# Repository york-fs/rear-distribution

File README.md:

# Rear Distribution Board

The rear distribution board is the central board of the LVS. It provides fusing for all other LVS components and
interfaces with the front, TSAC, and TS box distribution boards, as well as the inverter via AMPSEAL connections.

[Latest Release](https://github.com/york-fs/rear-distribution/releases/latest)
[Interactive BOM](https://york-fs.github.io/rear-distribution/ibom.html)

## Features

* **Blade Fuse Holders for All Other LVS components**
* **Fused 12 V and Shutdown Monitoring**
* **On-board microSD Slot**
* **UART Output for Radio Communication**

## Cloning

A recursive clone must be used to download the `kicad-library` repository:

    git clone --recursive https://github.com/york-fs/rear-distribution.git

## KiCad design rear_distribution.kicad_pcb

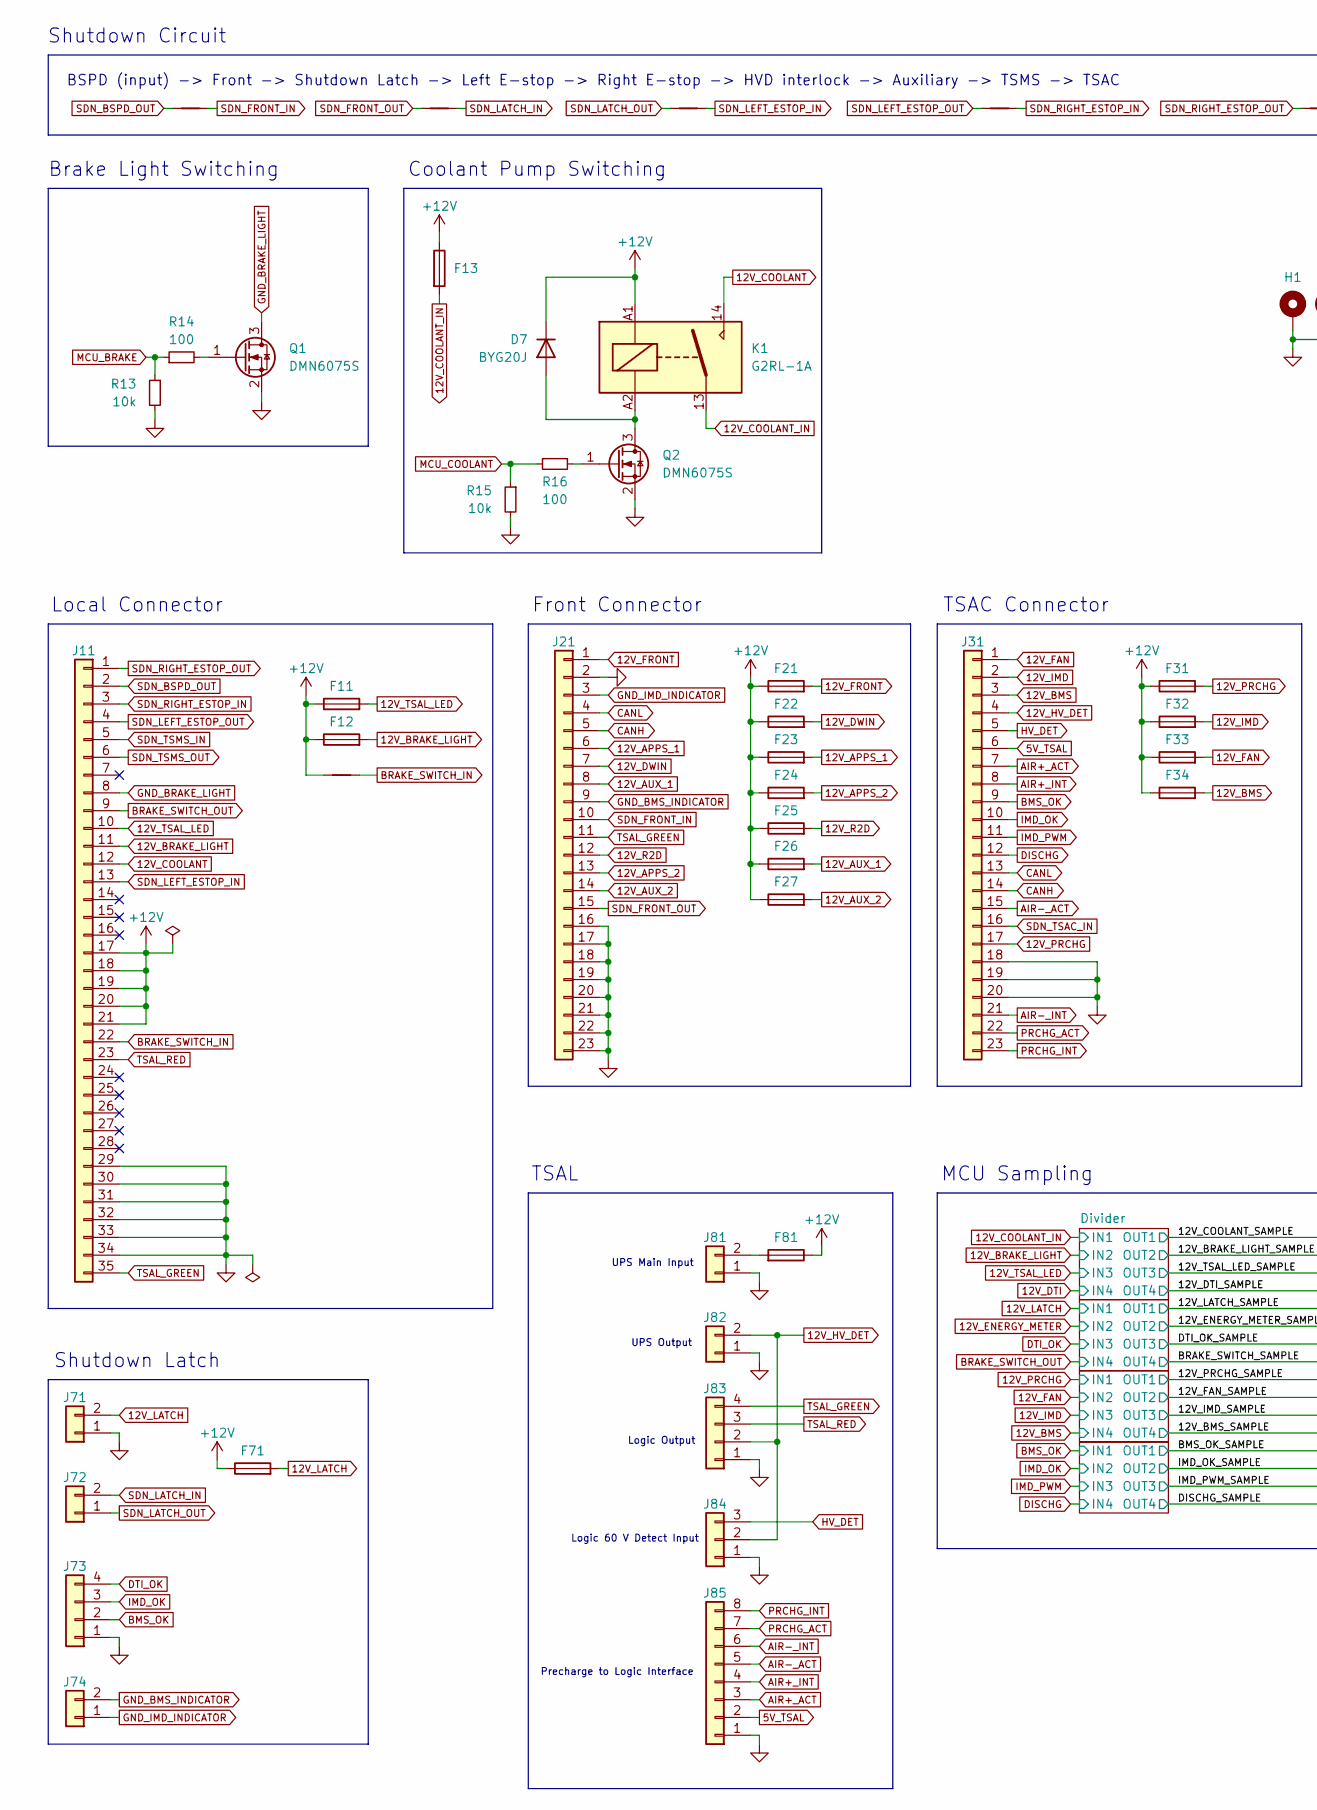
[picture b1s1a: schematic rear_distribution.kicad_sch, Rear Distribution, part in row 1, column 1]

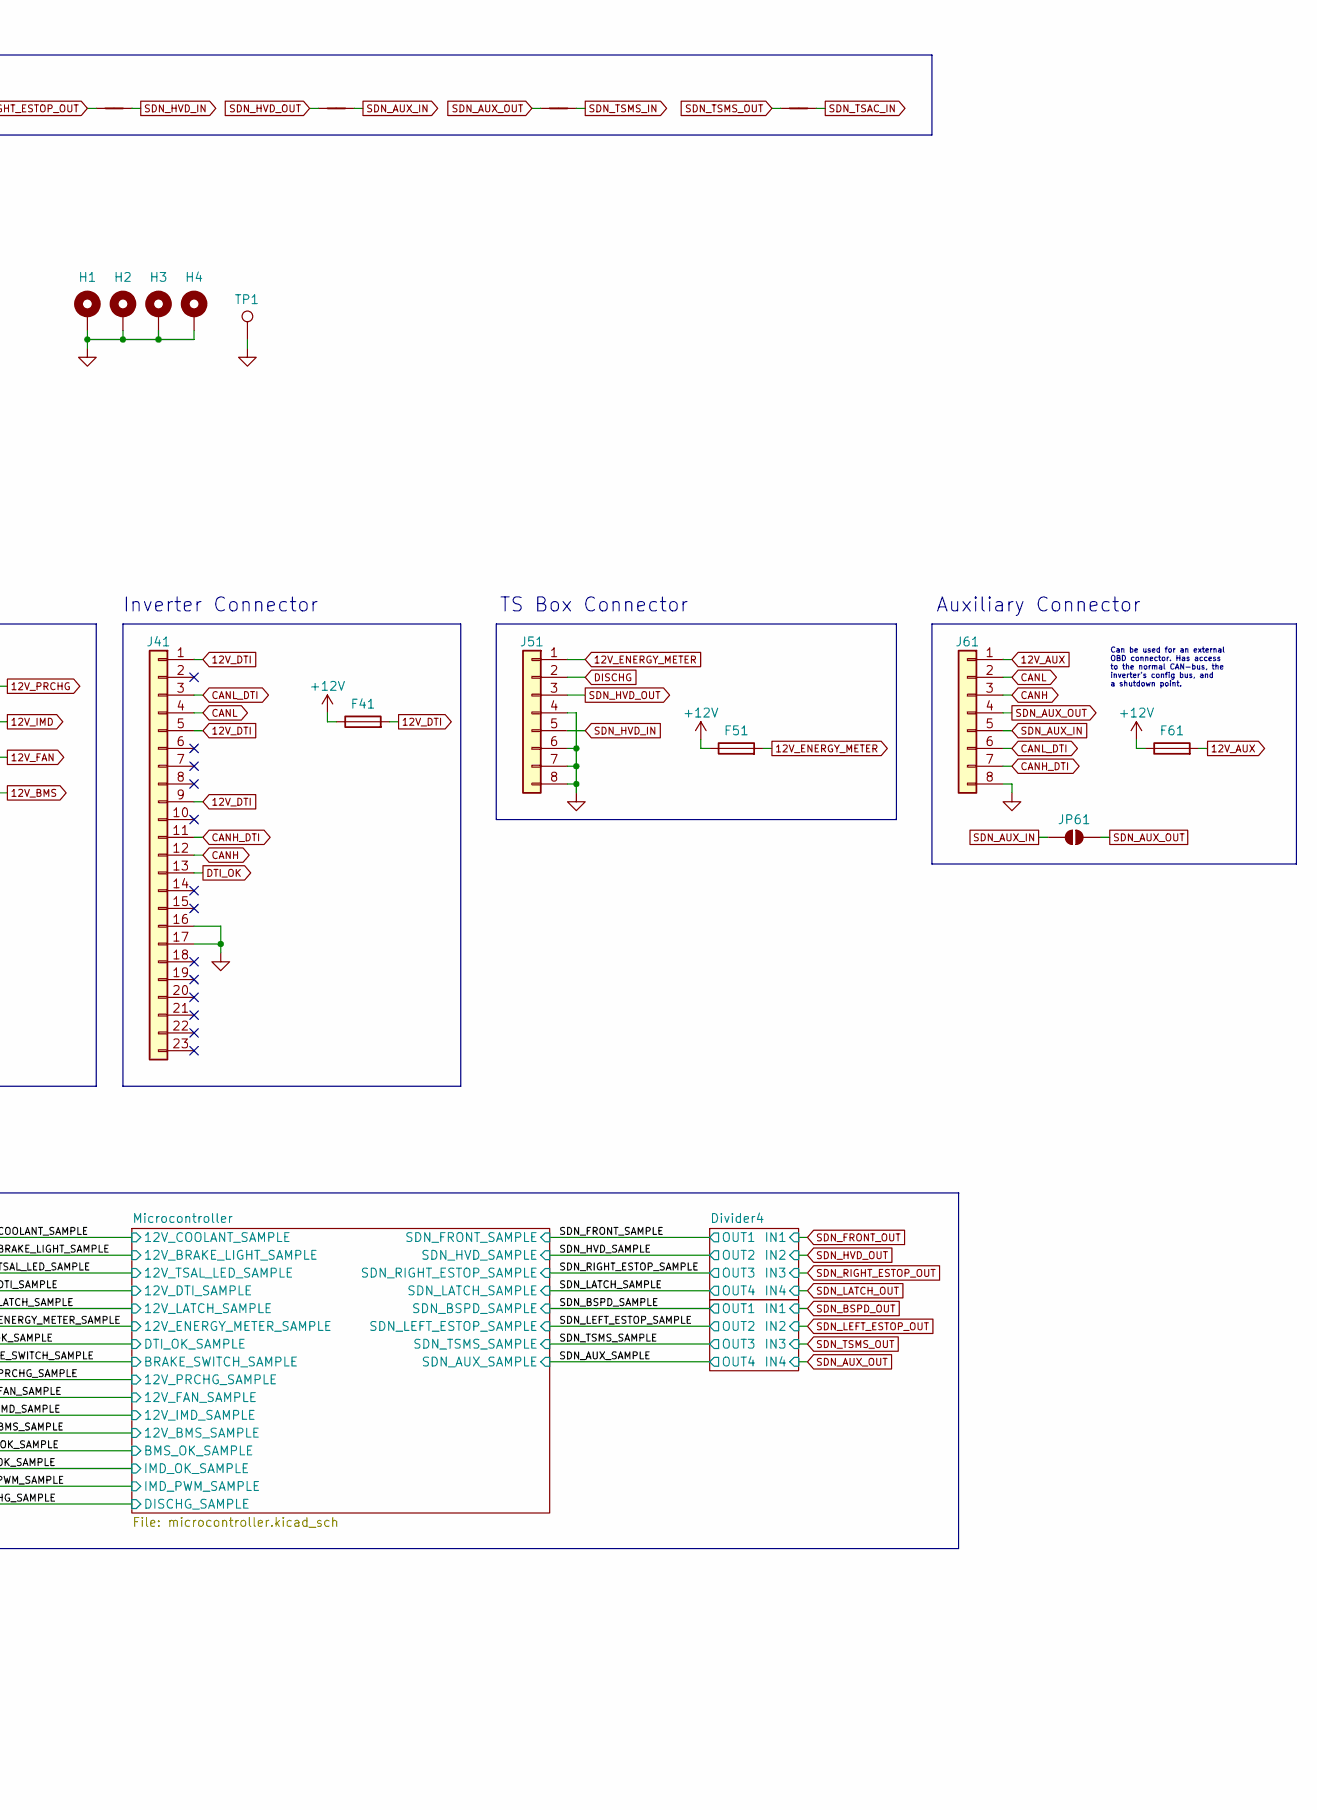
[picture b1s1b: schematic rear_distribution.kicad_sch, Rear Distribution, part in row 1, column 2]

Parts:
D7: BYG20J; D_SMA; Mfr # BYG20J-E3/TR; DigiKey # BYG20J-E3/TR3GICT-ND
F11, F12, F13, F21, F22, F23, F24, F25, F26, F27, F31, F32, F33, F34, F41, F51, F61, F71, F81: Fuse; Keystone_3557-2; Mfr # 3557-2; DigiKey # 36-3557-2-ND
H1, H2, H3, H4: MountingHole_Pad; MountingHole_3.2mm_M3_Pad_Via
J11: Conn_01x35; AMPSEAL-35-776163; Mfr # 776163-1; DigiKey # A106460-ND
J21, J31, J41: Conn_01x23; AMPSEAL-23-776087; Mfr # 776087-1; DigiKey # A107007-ND
J51, J61: Conn_01x08; AMPSEAL-8-776280; Mfr # 776280-1; DigiKey # 776280-1-ND
J71, J81: Conn_01x02; MolexMicrofitPlus1x2; Mfr # 2157601022; DigiKey # 900-2157601022-ND
J72: Conn_01x02; MolexMicrofitPlus1x2; Mfr # 2157601032; DigiKey # 900-2157601032-ND
J73, J83: Conn_01x04; MolexMicrofitPlus1x4; Mfr # 2157601004; DigiKey # 900-2157601004-ND
J74, J82: Conn_01x02; MolexMicrofitPlus1x2; Mfr # 2157601002; DigiKey # 900-2157601002-ND
J84: Conn_01x03; MolexMicrofitPlus1x3; Mfr # 2157601003; DigiKey # 900-2157601003-ND
J85: Conn_01x08; MolexMicrofitPlus1x8; Mfr # 2157601008; DigiKey # 900-2157601008-ND
JP61: SolderJumper_2_Open; SolderJumper-2_P1.3mm_Open_RoundedPad1.0x1.5mm
K1: G2RL-1A; Relay_SPST_Omron_G2RL-1A; Mfr # G2RL-1A-DC12; DigiKey # Z140-ND
NT2, NT3, NT4, NT5, NT6, NT7, NT8, NT9, NT10: NetTie_2; NetTie-2_SMD_Pad0.5mm
Q1, Q2: DMN6075S; SOT-23; Mfr # DMN6075S-7; DigiKey # DMN6075S-7DICT-ND
R13, R15: 10k; R_0603_1608Metric; Mfr # 0603WAF1002T5E; LCSC # C25804
R14, R16: 100; R_0603_1608Metric
TP1: TestPoint; TestPoint_Keystone_5019_Miniature; Mouser # 534-5019; DigiKey # 36-5019CT-ND

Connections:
5V_TSAL: J31.6, J85.2
12V_APPS_1: F23.2, J21.6
12V_APPS_2: F24.2, J21.13
12V_AUX: F61.2, J61.1
12V_AUX_1: F26.2, J21.8
12V_AUX_2: F27.2, J21.14
12V_BMS: F34.2, J31.3; also elsewhere on the board
12V_BRAKE_LIGHT: F12.2, J11.11; also elsewhere on the board
12V_COOLANT: J11.12, K1.14
12V_COOLANT_IN: F13.2, K1.13; also elsewhere on the board
12V_DTI: F41.2, J41.1, J41.5, J41.9; also elsewhere on the board
12V_DWIN: F22.2, J21.7
12V_ENERGY_METER: F51.2, J51.1; also elsewhere on the board
12V_FAN: F33.2, J31.1; also elsewhere on the board
12V_FRONT: F21.2, J21.1
12V_HV_DET: J31.4, J82.2, J83.2, J84.2
12V_IMD: F32.2, J31.2; also elsewhere on the board
12V_LATCH: F71.2, J71.2; also elsewhere on the board
12V_PRCHG: F31.2, J31.17; also elsewhere on the board
12V_R2D: F25.2, J21.12
12V_TSAL_LED: F11.2, J11.10; also elsewhere on the board
+12V: D7.1 (K), F11.1, F12.1, F13.1, F21.1, F22.1, F23.1, F24.1, F25.1, F26.1, F27.1, F31.1, F32.1, F33.1, F34.1, F41.1, F51.1, F61.1, F71.1, F81.1, J11.17, J11.18, J11.19, J11.20, J11.21, K1.A1, NT2.1; also elsewhere on the board
AIR+_ACT: J31.7, J85.3
AIR+_INT: J31.8, J85.4
AIR-_ACT: J31.15, J85.5
AIR-_INT: J31.21, J85.6
BMS_OK: J31.9, J73.2; also elsewhere on the board
BRAKE_SWITCH_IN: J11.22, NT2.2
BRAKE_SWITCH_OUT: J11.9; also elsewhere on the board
CANH: J21.5, J31.14, J41.12, J61.3; also elsewhere on the board
CANH_DTI: J41.11, J61.7
CANL: J21.4, J31.13, J41.4, J61.2; also elsewhere on the board
CANL_DTI: J41.3, J61.6
DISCHG: J31.12, J51.2; also elsewhere on the board
DTI_OK: J41.13, J73.4; also elsewhere on the board
GND: H1.1, H2.1, H3.1, H4.1, J11.29, J11.30, J11.31, J11.32, J11.33, J11.34, J21.2, J21.16, J21.17, J21.18, J21.19, J21.20, J21.21, J21.22, J21.23, J31.18, J31.19, J31.20, J41.16, J41.17, J51.4, J51.6, J51.7, J51.8, J61.8, J71.1, J73.1, J81.1, J82.1, J83.1, J84.1, J85.1, Q1.2 (S), Q2.2 (S), R13.2, R15.2, TP1.1; also elsewhere on the board
GND_BMS_INDICATOR: J21.9, J74.2
GND_BRAKE_LIGHT: J11.8, Q1.3 (D)
GND_IMD_INDICATOR: J21.3, J74.1
HV_DET: J31.5, J84.3
IMD_OK: J31.10, J73.3; also elsewhere on the board
IMD_PWM: J31.11; also elsewhere on the board
MCU_BRAKE: R13.1, R14.1; also elsewhere on the board
MCU_COOLANT: R15.1, R16.1; also elsewhere on the board
unnamed: D7.2 (A), K1.A2, Q2.3 (D)
unnamed: F81.2, J81.2
unnamed: Q1.1 (G), R14.2
unnamed: Q2.1 (G), R16.2
PRCHG_ACT: J31.22, J85.7
PRCHG_INT: J31.23, J85.8
SDN_AUX_IN: J61.5, JP61.1 (A), NT8.2
SDN_AUX_OUT: J61.4, JP61.2 (B), NT9.1; also elsewhere on the board
SDN_BSPD_OUT: J11.2, NT3.1; also elsewhere on the board
SDN_FRONT_IN: J21.10, NT3.2
SDN_FRONT_OUT: J21.15, NT4.1; also elsewhere on the board
SDN_HVD_IN: J51.5, NT7.2
SDN_HVD_OUT: J51.3, NT8.1; also elsewhere on the board
SDN_LATCH_IN: J72.2, NT4.2
SDN_LATCH_OUT: J72.1, NT5.1; also elsewhere on the board
SDN_LEFT_ESTOP_IN: J11.13, NT5.2
SDN_LEFT_ESTOP_OUT: J11.4, NT6.1; also elsewhere on the board
SDN_RIGHT_ESTOP_IN: J11.3, NT6.2
SDN_RIGHT_ESTOP_OUT: J11.1, NT7.1; also elsewhere on the board
SDN_TSAC_IN: J31.16, NT10.2
SDN_TSMS_IN: J11.5, NT9.2
SDN_TSMS_OUT: J11.6, NT10.1; also elsewhere on the board
TSAL_GREEN: J11.35, J21.11, J83.4
TSAL_RED: J11.23, J83.3

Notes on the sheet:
TSAL
Logic Output
UPS Main Input
Inverter Connector
UPS Output
Logic 60 V Detect Input
Auxiliary Connector
TSAC Connector
Local Connector
Precharge to Logic Interface
MCU Sampling
Can be used for an external OBD connector. Has access to the normal CAN-bus, the inverter's config bus, and a shutdown point.
Front Connector
BSPD (input) -> Front -> Shutdown Latch -> Left E-stop -> Right E-stop -> HVD interlock -> Auxiliary -> TSMS -> TSAC
Brake Light Switching
Shutdown Latch
Shutdown Circuit
Coolant Pump Switching
TS Box Connector

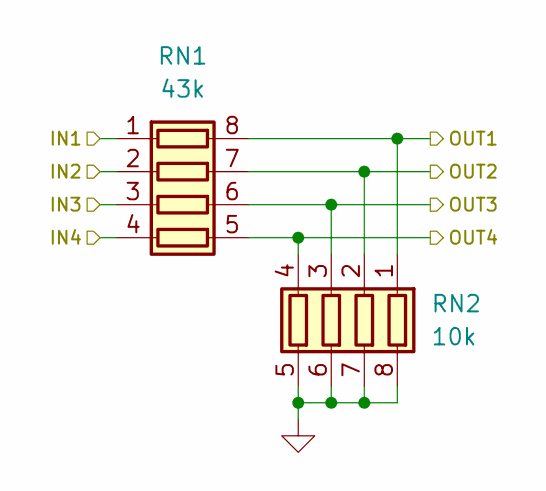
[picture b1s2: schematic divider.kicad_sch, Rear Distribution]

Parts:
RN1: 43k; R_Array_Convex_4x1206; Mfr # YC324-JK-0747KL; DigiKey # 13-YC324-JK-0747KLCT-ND
RN2: 10k; R_Array_Convex_4x1206; Mfr # YC324-FK-0710KL; DigiKey # 13-YC324-FK-0710KLCT-ND

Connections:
12V_BRAKE_LIGHT: RN1.2 (R2.1); also elsewhere on the board
12V_COOLANT_IN: RN1.1 (R1.1); also elsewhere on the board
12V_DTI: RN1.4 (R4.1); also elsewhere on the board
12V_TSAL_LED: RN1.3 (R3.1); also elsewhere on the board
/12V_BRAKE_LIGHT_SAMPLE: RN1.7 (R2.2), RN2.2 (R2.1); also elsewhere on the board
/12V_COOLANT_SAMPLE: RN1.8 (R1.2), RN2.1 (R1.1); also elsewhere on the board
/12V_DTI_SAMPLE: RN1.5 (R4.2), RN2.4 (R4.1); also elsewhere on the board
/12V_TSAL_LED_SAMPLE: RN1.6 (R3.2), RN2.3 (R3.1); also elsewhere on the board
GND: RN2.5 (R4.2), RN2.6 (R3.2), RN2.7 (R2.2), RN2.8 (R1.2); also elsewhere on the board

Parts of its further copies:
RN3, RN5, RN7, RN9, RN11: 43k; R_Array_Convex_4x1206; Mfr # YC324-JK-0747KL; DigiKey # 13-YC324-JK-0747KLCT-ND
RN4, RN6, RN8, RN10, RN12: 10k; R_Array_Convex_4x1206; Mfr # YC324-FK-0710KL; DigiKey # 13-YC324-FK-0710KLCT-ND

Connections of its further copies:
12V_BMS: RN5.4 (R4.1); also elsewhere on the board
12V_ENERGY_METER: RN3.2 (R2.1); also elsewhere on the board
12V_FAN: RN5.2 (R2.1); also elsewhere on the board
12V_IMD: RN5.3 (R3.1); also elsewhere on the board
12V_LATCH: RN3.1 (R1.1); also elsewhere on the board
12V_PRCHG: RN5.1 (R1.1); also elsewhere on the board
/12V_BMS_SAMPLE: RN5.5 (R4.2), RN6.4 (R4.1); also elsewhere on the board
/12V_ENERGY_METER_SAMPLE: RN3.7 (R2.2), RN4.2 (R2.1); also elsewhere on the board
/12V_FAN_SAMPLE: RN5.7 (R2.2), RN6.2 (R2.1); also elsewhere on the board
/12V_IMD_SAMPLE: RN5.6 (R3.2), RN6.3 (R3.1); also elsewhere on the board
/12V_LATCH_SAMPLE: RN3.8 (R1.2), RN4.1 (R1.1); also elsewhere on the board
/12V_PRCHG_SAMPLE: RN5.8 (R1.2), RN6.1 (R1.1); also elsewhere on the board
/BMS_OK_SAMPLE: RN7.8 (R1.2), RN8.1 (R1.1); also elsewhere on the board
/BRAKE_SWITCH_SAMPLE: RN3.5 (R4.2), RN4.4 (R4.1); also elsewhere on the board
/DISCHG_SAMPLE: RN7.5 (R4.2), RN8.4 (R4.1); also elsewhere on the board
/DTI_OK_SAMPLE: RN3.6 (R3.2), RN4.3 (R3.1); also elsewhere on the board
/IMD_OK_SAMPLE: RN7.7 (R2.2), RN8.2 (R2.1); also elsewhere on the board
/IMD_PWM_SAMPLE: RN7.6 (R3.2), RN8.3 (R3.1); also elsewhere on the board
/SDN_AUX_SAMPLE: RN11.5 (R4.2), RN12.4 (R4.1); also elsewhere on the board
/SDN_BSPD_SAMPLE: RN11.8 (R1.2), RN12.1 (R1.1); also elsewhere on the board
/SDN_FRONT_SAMPLE: RN9.8 (R1.2), RN10.1 (R1.1); also elsewhere on the board
/SDN_HVD_SAMPLE: RN9.7 (R2.2), RN10.2 (R2.1); also elsewhere on the board
/SDN_LATCH_SAMPLE: RN9.5 (R4.2), RN10.4 (R4.1); also elsewhere on the board
/SDN_LEFT_ESTOP_SAMPLE: RN11.7 (R2.2), RN12.2 (R2.1); also elsewhere on the board
/SDN_RIGHT_ESTOP_SAMPLE: RN9.6 (R3.2), RN10.3 (R3.1); also elsewhere on the board
/SDN_TSMS_SAMPLE: RN11.6 (R3.2), RN12.3 (R3.1); also elsewhere on the board
BMS_OK: RN7.1 (R1.1); also elsewhere on the board
BRAKE_SWITCH_OUT: RN3.4 (R4.1); also elsewhere on the board
DISCHG: RN7.4 (R4.1); also elsewhere on the board
DTI_OK: RN3.3 (R3.1); also elsewhere on the board
GND: RN4.5 (R4.2), RN4.6 (R3.2), RN4.7 (R2.2), RN4.8 (R1.2), RN6.5 (R4.2), RN6.6 (R3.2), RN6.7 (R2.2), RN6.8 (R1.2), RN8.5 (R4.2), RN8.6 (R3.2), RN8.7 (R2.2), RN8.8 (R1.2), RN10.5 (R4.2), RN10.6 (R3.2), RN10.7 (R2.2), RN10.8 (R1.2), RN12.5 (R4.2), RN12.6 (R3.2), RN12.7 (R2.2), RN12.8 (R1.2); also elsewhere on the board
IMD_OK: RN7.2 (R2.1); also elsewhere on the board
IMD_PWM: RN7.3 (R3.1); also elsewhere on the board
SDN_AUX_OUT: RN11.4 (R4.1); also elsewhere on the board
SDN_BSPD_OUT: RN11.1 (R1.1); also elsewhere on the board
SDN_FRONT_OUT: RN9.1 (R1.1); also elsewhere on the board
SDN_HVD_OUT: RN9.2 (R2.1); also elsewhere on the board
SDN_LATCH_OUT: RN9.4 (R4.1); also elsewhere on the board
SDN_LEFT_ESTOP_OUT: RN11.2 (R2.1); also elsewhere on the board
SDN_RIGHT_ESTOP_OUT: RN9.3 (R3.1); also elsewhere on the board
SDN_TSMS_OUT: RN11.3 (R3.1); also elsewhere on the board

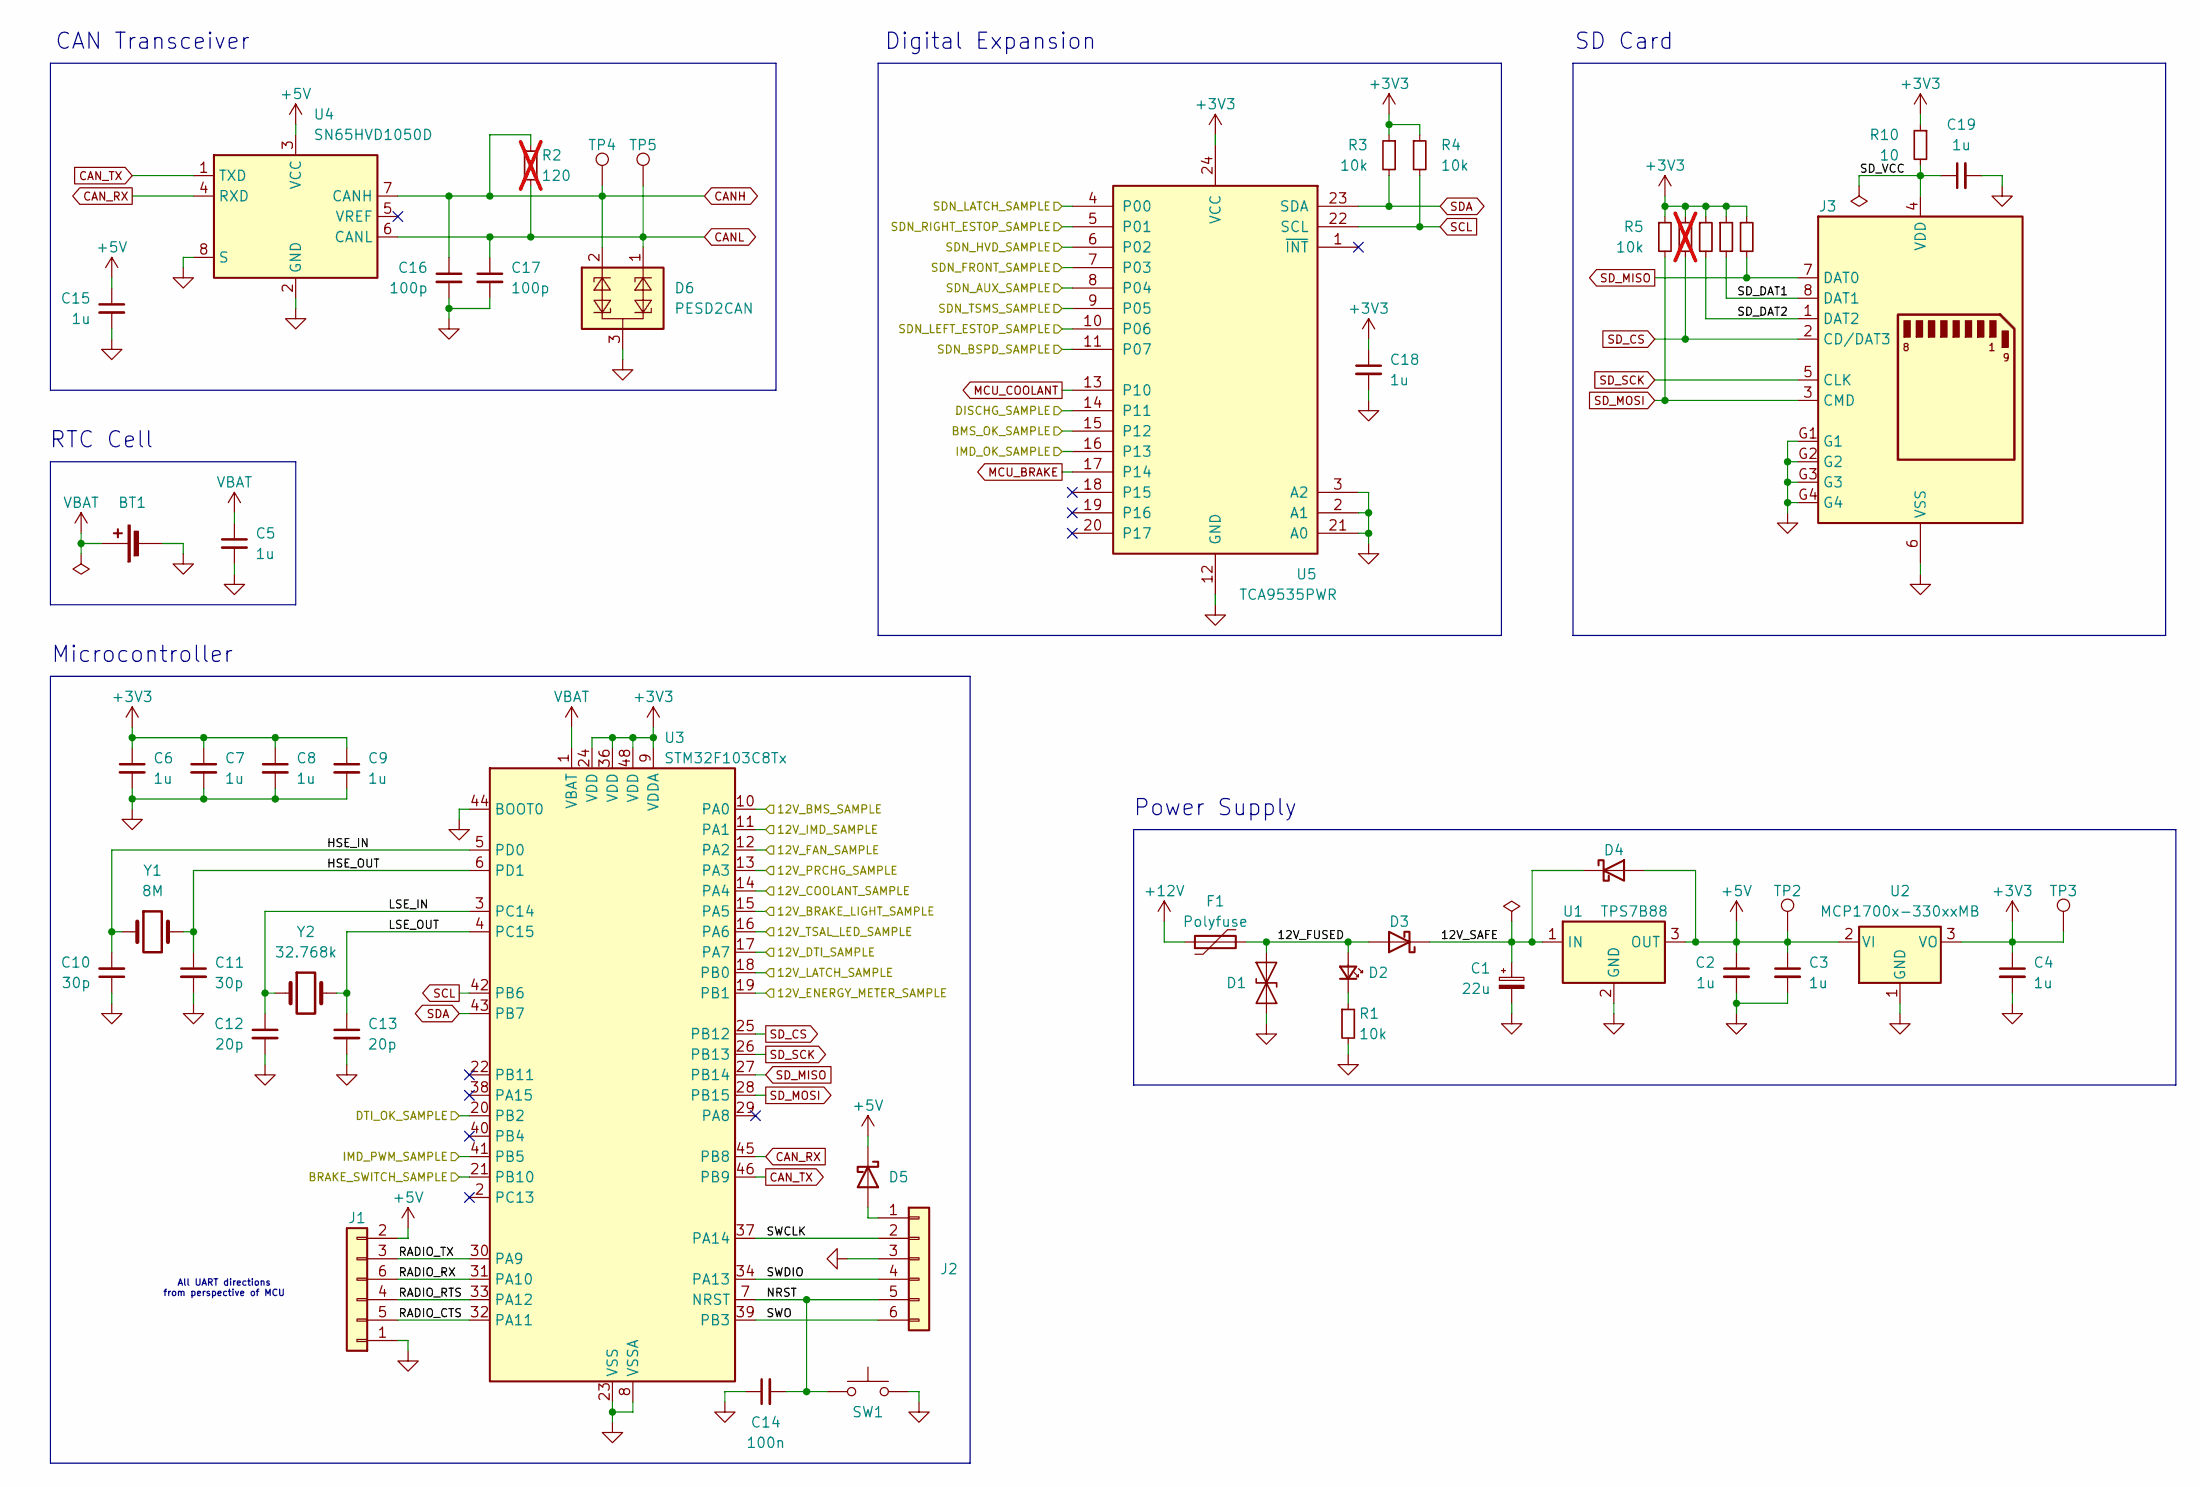
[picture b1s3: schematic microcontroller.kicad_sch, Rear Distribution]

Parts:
BT1: Battery_Cell; BAT-SMD_BS-CR2032-8
C1: 22u; CP_Elec_6.3x7.7; Mfr # EEEFK1J220XP; DigiKey # PCE3821CT-ND
C2, C3, C4, C5, C6, C7, C8, C9, C15, C18, C19: 1u; C_0603_1608Metric; Mfr # CL10B105KB8NQNC; LCSC # C5199872
C10, C11: 30p; C_0603_1608Metric; Mfr # GQM1875C2E300GB12D; DigiKey # 490-GQM1875C2E300GB12DCT-ND
C12, C13: 20p; C_0603_1608Metric
C14: 100n; C_0603_1608Metric; Mfr # CL10B104KB8NNNC; DigiKey # 1276-1000-1-ND
C16, C17: 100p; C_0603_1608Metric; Mfr # GCM1885C2A101JA16D; DigiKey # 490-4771-1-ND
D1: SMAJ24CA; D_SMA; Mfr # SMAJ24CA; DigiKey # SMAJ24CALFCT-ND
D2: LED_Small; LED_0603_1608Metric; Mfr # NCD0603R1; LCSC # C84263
D3, D4, D5: D_Schottky; D_SOD-323; Mfr # NSR0530H; DigiKey # NSR0530HT1GOSCT-ND
D6: PESD2CAN; SOT-23; Mfr # PESD2CAN,215; DigiKey # 1727-3891-1-ND
F1: Polyfuse; C_0805_2012Metric; Mfr # 0805L010/24YR; DigiKey # F11311CT-ND
J1: Conn_01x06; MolexMicrofitPlus2x3; Mfr # 2125280600; DigiKey # 900-2125280600-ND
J2: Conn_01x06; IDC-Connector-2x3; Mfr # HX JN1.27-2x3P ZZ H4.9; LCSC # C42372545
J3: 47219-2001; Molex_SD_Slot_47219-2001; Mfr # 472192001; DigiKey # WM6698CT-ND
R1, R3, R4, R5, R7, R8, R9: 10k; R_0603_1608Metric; Mfr # 0603WAF1002T5E; LCSC # C25804
R2: 120; R_0603_1608Metric; not fitted
R6: 10k; R_0603_1608Metric; Mfr # 0603WAF1002T5E; LCSC # C25804; not fitted
R10: 10; R_0603_1608Metric
SW1: SW_Push; SW_Push_1P1T_NO_Vertical_Wuerth_434133025816; Mfr # SKRPACE010; DigiKey # 4809-SKRPACE010CT-ND
TP2, TP3: TestPoint; TestPoint_Keystone_5000-5004_Miniature; Mouser # 534-5000; DigiKey # 36-5000-ND
TP4, TP5: TestPoint; TestPoint_THTPad_D2.0mm_Drill1.0mm
U1: TPS7B88; TO-252-2; Mfr # TPS7B8850QKVURQ1; DigiKey # 296-TPS7B8850QKVURQ1CT-ND
U2: MCP1700x-330xxMB; SOT-89-3; Mfr # MCP1700T-3302E/MB; DigiKey # MCP1700T3302EMBCT-ND
U3: STM32F103C8Tx; LQFP-48_7x7mm_P0.5mm; Mfr # STM32F103C8T6; DigiKey # 497-17666-1-ND
U4: SN65HVD1050D; SOIC-8_3.9x4.9mm_P1.27mm; Mfr # SN65HVD1050DR; DigiKey # 296-26335-1-ND
U5: TCA9535PWR; TSSOP-24_4.4x7.8mm_P0.65mm; Mfr # TCA9535PWR; DigiKey # 296-25129-1-ND
Y1: 8M; Crystal_SMD_5032-2Pin_5.0x3.2mm; Mfr # X50328MSB2GI; LCSC # C115962
Y2: 32.768k; Crystal_SMD_G8-2Pin_3.2x1.5mm

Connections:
+3V3: C4.1, C6.1, C7.1, C8.1, C9.1, C18.1, R3.1, R4.1, R5.1, R6.1, R7.1, R8.1, R9.1, R10.1, TP3.1, U2.3 (VO), U3.9 (VDDA), U3.24 (VDD), U3.36 (VDD), U3.48 (VDD), U5.24 (VCC)
+5V: C2.1, C3.1, C15.1, D4.2 (A), D5.1 (K), J1.2, TP2.1, U1.3 (OUT), U2.2 (VI), U4.3 (VCC)
+12V: F1.1; also elsewhere on the board
/12V_BMS_SAMPLE: U3.10 (PA0); also elsewhere on the board
/12V_BRAKE_LIGHT_SAMPLE: U3.15 (PA5); also elsewhere on the board
/12V_COOLANT_SAMPLE: U3.14 (PA4); also elsewhere on the board
/12V_DTI_SAMPLE: U3.17 (PA7); also elsewhere on the board
/12V_ENERGY_METER_SAMPLE: U3.19 (PB1); also elsewhere on the board
/12V_FAN_SAMPLE: U3.12 (PA2); also elsewhere on the board
/12V_IMD_SAMPLE: U3.11 (PA1); also elsewhere on the board
/12V_LATCH_SAMPLE: U3.18 (PB0); also elsewhere on the board
/12V_PRCHG_SAMPLE: U3.13 (PA3); also elsewhere on the board
/12V_TSAL_LED_SAMPLE: U3.16 (PA6); also elsewhere on the board
/BMS_OK_SAMPLE: U5.15 (P12); also elsewhere on the board
/BRAKE_SWITCH_SAMPLE: U3.21 (PB10); also elsewhere on the board
/DISCHG_SAMPLE: U5.14 (P11); also elsewhere on the board
/DTI_OK_SAMPLE: U3.20 (PB2); also elsewhere on the board
/IMD_OK_SAMPLE: U5.16 (P13); also elsewhere on the board
/IMD_PWM_SAMPLE: U3.41 (PB5); also elsewhere on the board
/Microcontroller/12V_FUSED: D1.2 (A2), D2.2 (A), D3.2 (A), F1.2
/Microcontroller/12V_SAFE: C1.1, D3.1 (K), D4.1 (K), U1.1 (IN)
/Microcontroller/HSE_IN: C10.2, U3.5 (PD0), Y1.1
/Microcontroller/HSE_OUT: C11.1, U3.6 (PD1), Y1.2
/Microcontroller/LSE_IN: C12.1, U3.3 (PC14), Y2.1
/Microcontroller/LSE_OUT: C13.1, U3.4 (PC15), Y2.2
/Microcontroller/NRST: C14.2, J2.5, SW1.1, U3.7 (NRST)
/Microcontroller/RADIO_CTS: J1.5, U3.32 (PA11)
/Microcontroller/RADIO_RTS: J1.4, U3.33 (PA12)
/Microcontroller/RADIO_RX: J1.6, U3.31 (PA10)
/Microcontroller/RADIO_TX: J1.3, U3.30 (PA9)
/Microcontroller/SD_DAT1: J3.8 (DAT1), R8.2
/Microcontroller/SD_DAT2: J3.1 (DAT2), R7.2
/Microcontroller/SD_VCC: C19.1, J3.4 (VDD), R10.2
/Microcontroller/SWCLK: J2.2, U3.37 (PA14)
/Microcontroller/SWDIO: J2.4, U3.34 (PA13)
/Microcontroller/SWO: J2.6, U3.39 (PB3)
/SDN_AUX_SAMPLE: U5.8 (P04); also elsewhere on the board
/SDN_BSPD_SAMPLE: U5.11 (P07); also elsewhere on the board
/SDN_FRONT_SAMPLE: U5.7 (P03); also elsewhere on the board
/SDN_HVD_SAMPLE: U5.6 (P02); also elsewhere on the board
/SDN_LATCH_SAMPLE: U5.4 (P00); also elsewhere on the board
/SDN_LEFT_ESTOP_SAMPLE: U5.10 (P06); also elsewhere on the board
/SDN_RIGHT_ESTOP_SAMPLE: U5.5 (P01); also elsewhere on the board
/SDN_TSMS_SAMPLE: U5.9 (P05); also elsewhere on the board
CANH: C16.1, D6.2 (C2), R2.1, TP4.1, U4.7 (CANH); also elsewhere on the board
CANL: C17.1, D6.1 (C1), R2.2, TP5.1, U4.6 (CANL); also elsewhere on the board
CAN_RX: U3.45 (PB8), U4.4 (RXD)
CAN_TX: U3.46 (PB9), U4.1 (TXD)
GND: BT1.2 (-), C1.2, C2.2, C3.2, C4.2, C5.2, C6.2, C7.2, C8.2, C9.2, C10.1, C11.2, C12.2, C13.2, C14.1, C15.2, C16.2, C17.2, C18.2, C19.2, D1.1 (A1), D6.3 (CC), J1.1, J2.3, J3.6 (VSS), J3.G1, J3.G2, J3.G3, J3.G4, R1.2, SW1.2, U1.2 (GND), U2.1 (GND), U3.8 (VSSA), U3.23 (VSS), U3.35 (VSS), U3.44 (BOOT0), U3.47 (VSS), U4.2 (GND), U4.8 (S), U5.2 (A1), U5.3 (A2), U5.12 (GND), U5.21 (A0); also elsewhere on the board
MCU_BRAKE: U5.17 (P14); also elsewhere on the board
MCU_COOLANT: U5.13 (P10); also elsewhere on the board
unnamed: D2.1 (K), R1.1
unnamed: D5.2 (A), J2.1
SCL: R4.2, U3.42 (PB6), U5.22 (SCL)
SDA: R3.2, U3.43 (PB7), U5.23 (SDA)
SD_CS: J3.2 (CD/DAT3), R6.2, U3.25 (PB12)
SD_MISO: J3.7 (DAT0), R9.2, U3.27 (PB14)
SD_MOSI: J3.3 (CMD), R5.2, U3.28 (PB15)
SD_SCK: J3.5 (CLK), U3.26 (PB13)
VBAT: BT1.1 (+), C5.1, U3.1 (VBAT)

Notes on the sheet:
Microcontroller
RTC Cell
SD Card
Digital Expansion
CAN Transceiver
Power Supply
All UART directions from perspective of MCU

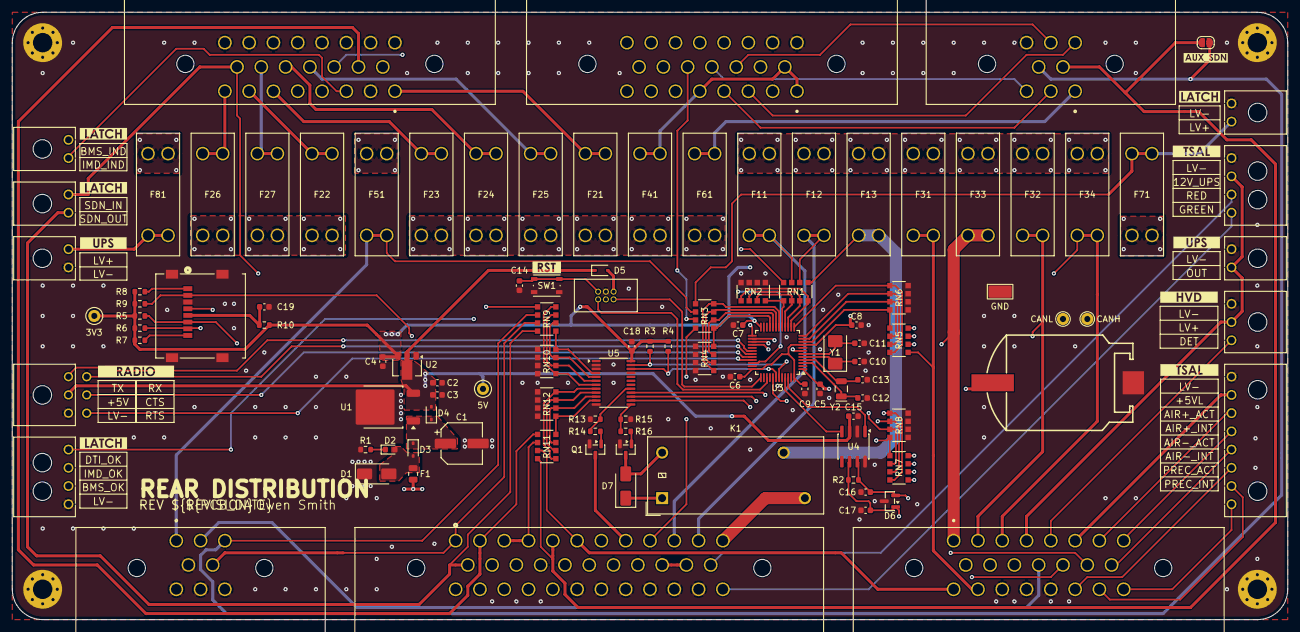
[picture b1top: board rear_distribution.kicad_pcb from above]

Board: 4 copper layers, 210.0 x 100.0 mm, 133 parts (1 on the bottom side), 122 nets.

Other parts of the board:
kibuzzard-6A35CDBD: G***; kibuzzard-6A35CDBD
kibuzzard-6A35CEAD: G***; kibuzzard-6A35CEAD
kibuzzard-6A35CF3E, kibuzzard-6A35CF3E#2: G***; kibuzzard-6A35CF3E
kibuzzard-6A35CF98: G***; kibuzzard-6A35CF98
kibuzzard-6A3571FC: G***; kibuzzard-6A3571FC
kibuzzard-6A3572FA: G***; kibuzzard-6A3572FA
kibuzzard-6A3574B6: G***; kibuzzard-6A3574B6
kibuzzard-6A35710C: G***; kibuzzard-6A35710C
kibuzzard-6A35750C: G***; kibuzzard-6A35750C
kibuzzard-6910BB45: G***; kibuzzard-6910BB45
kibuzzard-6940937D: G***; kibuzzard-6940937D

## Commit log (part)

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2026-06-16 schematic: Tentatively finish major schematic parts
2026-06-16 schematic: Re-annotate and add RTC battery
2026-06-16 schematic: Assign footprints and fill most of BOM
2026-06-16 *: Setup PCB
2026-06-18 pcb: Add layout progress so far
2026-06-19 *: Tentatively finish everything
2026-06-19 pcb: Move RN6 designator
2026-06-19 pcb: Add model for 2x3 MF+ and fix fuse model alignment
2026-06-19 *: Add CAN test points
2026-06-19 pcb: Cleanup silkscreen some more
2026-06-22 pcb: Setup AISLER push
2026-06-25 schematic: Cleanup BOM
2026-06-25 schematic: Cleanup root schematic page
2026-06-25 ci: Add KiCad CI
2026-06-25 meta: Add README
